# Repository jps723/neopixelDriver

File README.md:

# Neopixel Driver Build Notes 2/2/20

This project is in partnership with [Bantam Tools](https://www.bantamtools.com)

**Design Notes:**

This driver board is intended to facilitate large Neopixel arrays through split power/ground lines for power injection.  The board is split into two sides as power and ground planes.  A 1000uF capacitor sits between them to prevent damage to the Neopixels from a rush of current when first powering them on.  A 470Ω resistor lies in series with the data line so as to prevent damage to the first pixel due to spikes in the signal.

The power and ground planes feed into 3 terminal blocks, respectively, allowing for up to 6 lines of power injection.  Additionally, there are 4 mounting holes for M3 screws. The graphic below shows a potential use case.

*Note: This is intended for use with 5v microcontrollers.  Controllers outputting 3.3v or similar (i.e. raspberry pi/teensy) may require level shifting on the data line.

# Build Process
**Bit:** 1/32”
**Mill Time:** ~5mins

It’s easiest to solder in this order:
```
1. Resistor
2. Capacitor
3. Screw Terminals
```

**Test**

Run Strandtest from the Adafruit Neopixel library examples.  Pin6 is the default data pin.  Test with a voltmeter at each of the screw terminals.

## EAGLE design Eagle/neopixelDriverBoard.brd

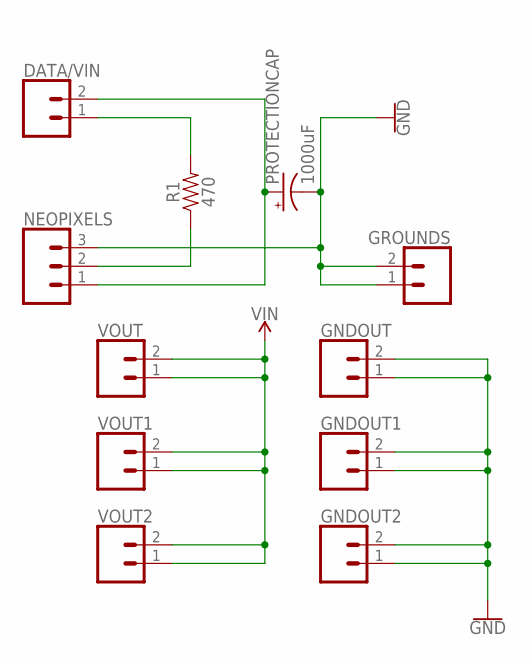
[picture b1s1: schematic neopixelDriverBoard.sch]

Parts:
DATA/VIN: CONN_025MM; SCREWTERMINAL-5MM-2
GNDOUT, GNDOUT1, GNDOUT2: CONN_025MM; SCREWTERMINAL-5MM-2
GROUNDS: CONN_025MM; SCREWTERMINAL-5MM-2
NEOPIXELS: CONN_03-SCREW-5MM; SCREWTERMINAL-5MM-3
PROTECTIONCAP: 1000uF; CPOL-RADIAL-5MM-10MM
R1: 470; AXIAL-0.3-KIT
VOUT, VOUT1, VOUT2: CONN_025MM; SCREWTERMINAL-5MM-2

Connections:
DATA: NEOPIXELS.2, R1.P$1 (1)
GND: GNDOUT.1, GNDOUT.2, GNDOUT1.1, GNDOUT1.2, GNDOUT2.1, GNDOUT2.2, GROUNDS.1, GROUNDS.2, NEOPIXELS.3, PROTECTIONCAP.-
unnamed: DATA/VIN.1, R1.P$2 (2)
VIN: DATA/VIN.2, NEOPIXELS.1, PROTECTIONCAP.+, VOUT.1, VOUT.2, VOUT1.1, VOUT1.2, VOUT2.1, VOUT2.2

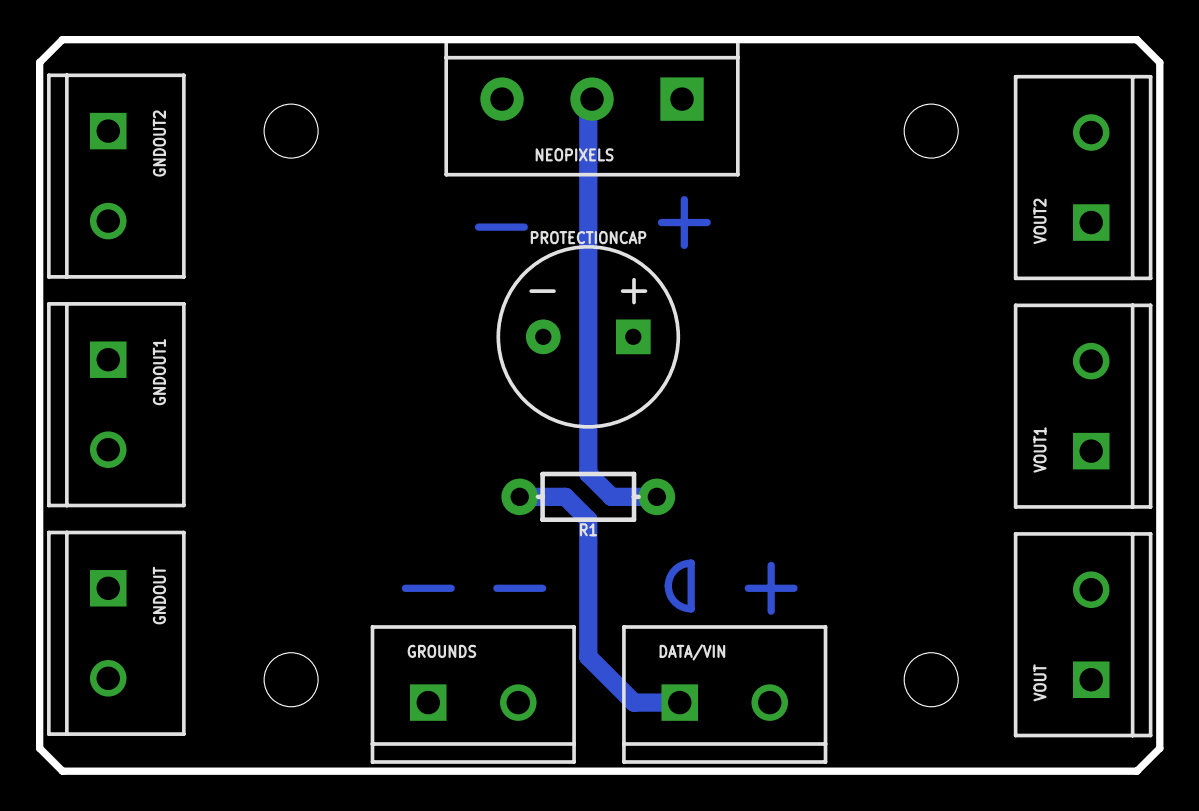
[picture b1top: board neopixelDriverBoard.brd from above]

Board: 2 copper layers, 62.2 x 40.6 mm, 11 parts (0 on the bottom side), 4 nets.

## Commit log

2020-10-30 added bantam tools credit
2021-04-27 added higher quality diagram
2021-04-27 added image path

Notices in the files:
parts and their libraries:
SparkFun-Connectors: Licensing: Creative Commons ShareAlike 4.0 International - https://creativecommons.org/licenses/by-sa/4.0
